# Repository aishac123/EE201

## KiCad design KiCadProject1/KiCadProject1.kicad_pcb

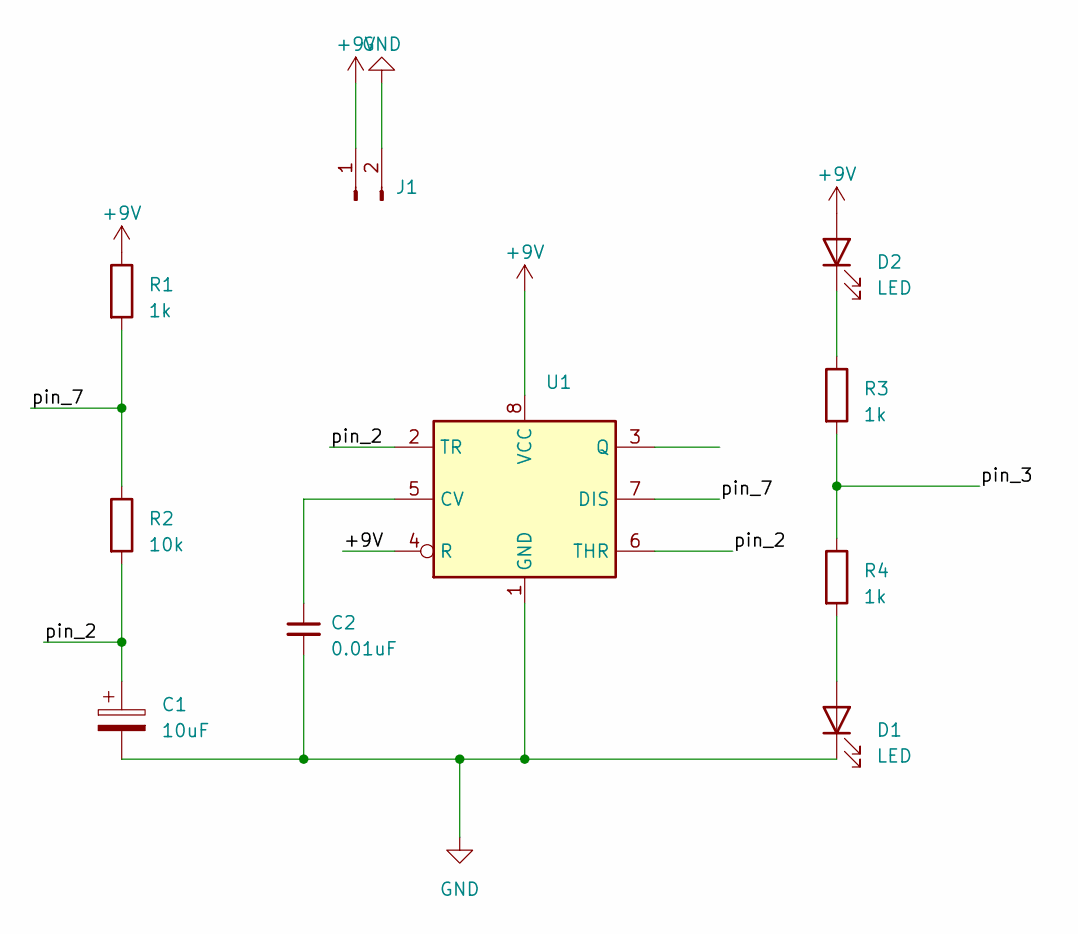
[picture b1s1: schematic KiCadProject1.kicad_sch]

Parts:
C1: 10uF; CP_EIA-3216-18_Kemet-A_Pad1.58x1.35mm_HandSolder
C2: 0.01uF; C_0805_2012Metric_Pad1.18x1.45mm_HandSolder
D1, D2: LED; LED_1206_3216Metric_Pad1.42x1.75mm_HandSolder
J1: JST_EH_S2B-EH_1x02_P2.50mm_Horizontal
R1, R3, R4: 1k; R_0805_2012Metric_Pad1.20x1.40mm_HandSolder
R2: 10k; R_0805_2012Metric_Pad1.20x1.40mm_HandSolder
U1: SOIC-8-1EP_3.9x4.9mm_P1.27mm_EP2.29x3mm

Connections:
+9V: D2.2 (A), J1.1, R1.1, U1.4 (R), U1.8 (VCC)
/pin_2: C1.1, R2.2, U1.2 (TR), U1.6 (THR)
/pin_3: R3.2, R4.1
/pin_7: R1.2, R2.1, U1.7 (DIS)
GND: C1.2, C2.2, D1.1 (K), J1.2, U1.1 (GND)
unnamed: D1.2 (A), R4.2
unnamed: D2.1 (K), R3.1
unnamed: C2.1, U1.5 (CV)

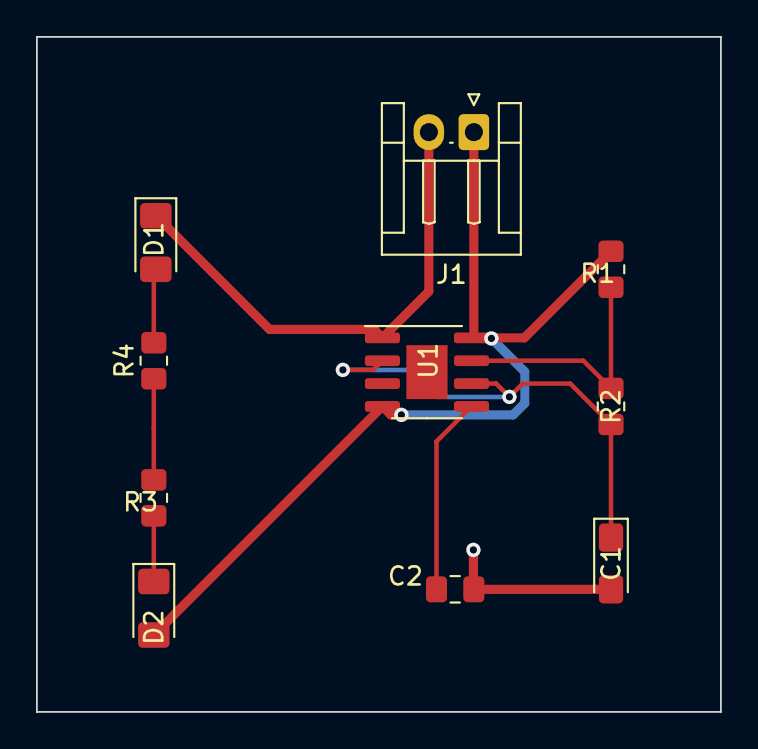
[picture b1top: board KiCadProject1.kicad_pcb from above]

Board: 2 copper layers, 38.0 x 37.5 mm, 10 parts (0 on the bottom side), 8 nets.

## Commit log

2023-03-30 adding README
2023-03-30 committing the next change
2023-03-30 committing first lines of about me
2023-03-30 commit new change
2023-03-30 change
2023-03-30 changed
2023-03-30 final changes
2023-04-20 finshed CAD file
2023-04-27 this is for arduino
2023-05-04 week 6 soldering activity
